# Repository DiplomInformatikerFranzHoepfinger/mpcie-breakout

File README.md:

# mpcie-breakout
https://osmocom.org/projects/mpcie-breakout/wiki --> advance this.

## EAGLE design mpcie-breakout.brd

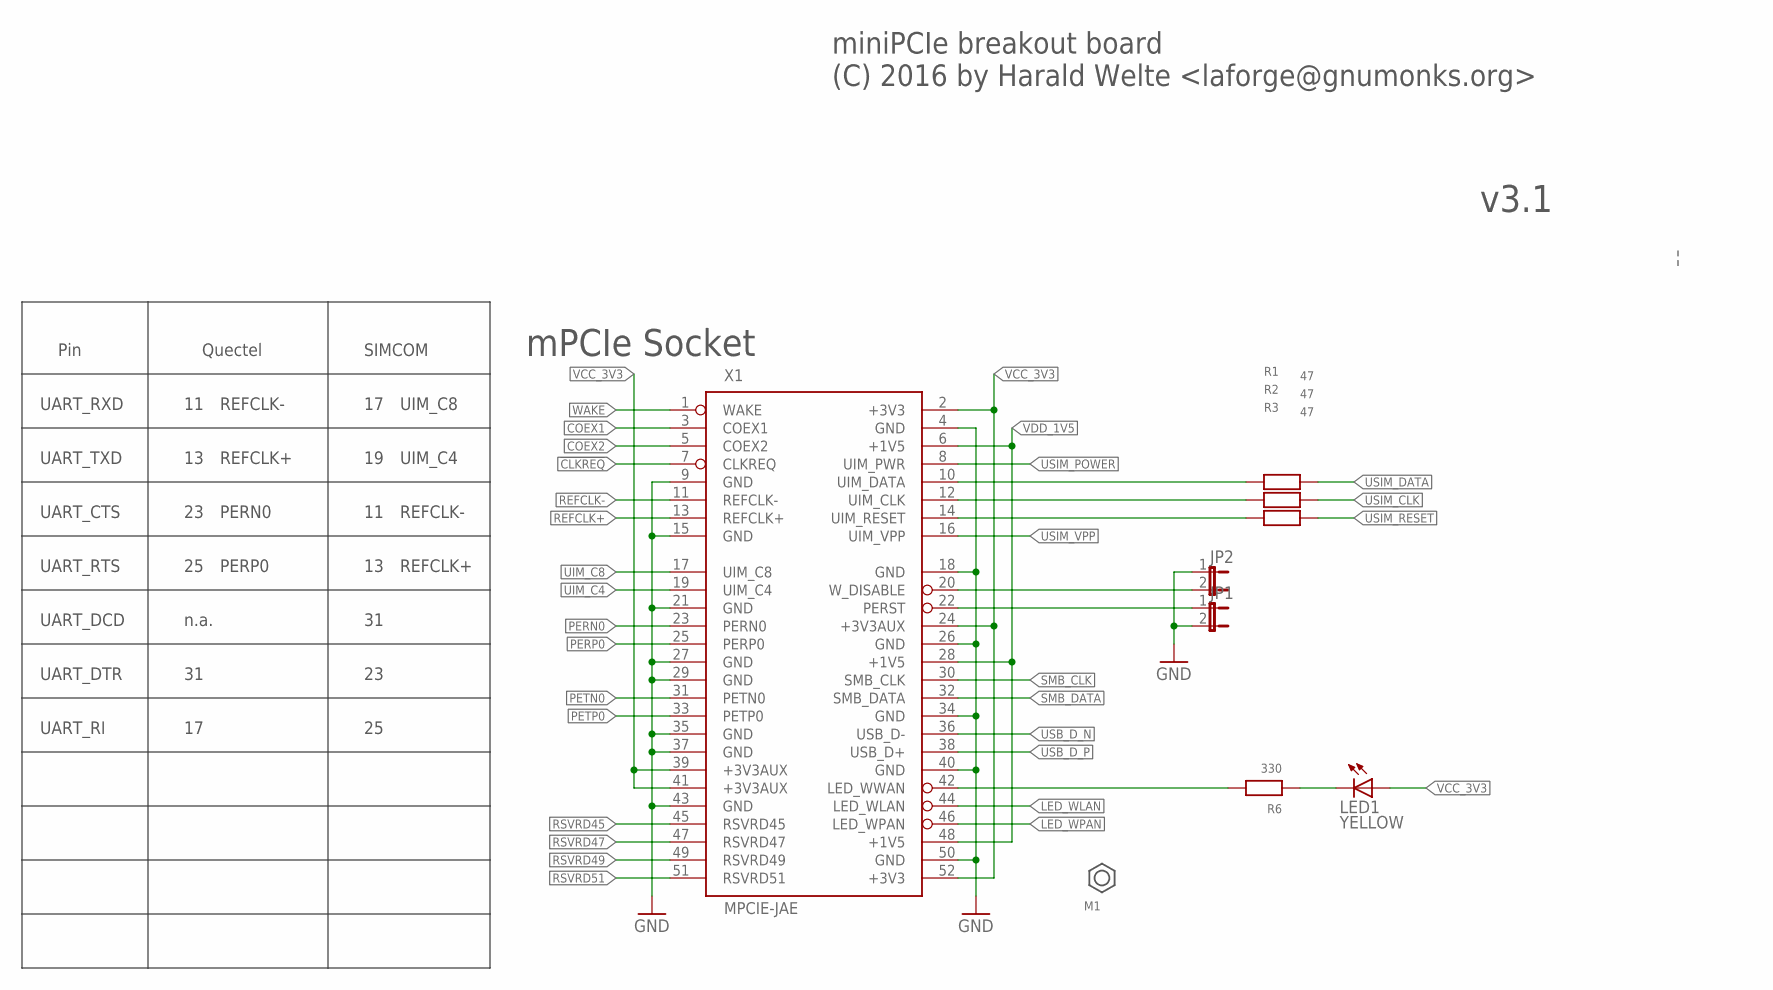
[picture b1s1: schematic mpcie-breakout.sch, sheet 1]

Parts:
JP1, JP2: JP1E; JP1; MANUFACTURERPARTNUMBER UNKNOWN MANUFACTURER PART NUMBER
LED1: YELLOW; CHIP-LED0603; MANUFACTURERPARTNUMBER UNKNOWN MANUFACTURER PART NUMBER
R1, R2, R3: 47; _0603; MANUFACTURERPARTNUMBER RC0603JR-0747RL
R6: 330; _0603; MANUFACTURERPARTNUMBER RC0603JR-07330RL
X1: MPCIE-JAE; MM60-52; MANUFACTURERPARTNUMBER MM60-52B1-E1-R650

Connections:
!CLKREQ: X1.7 (CLKREQ); also elsewhere on the board
COEX1: X1.3 (COEX1); also elsewhere on the board
COEX2: X1.5 (COEX2); also elsewhere on the board
GND: JP1.2, JP2.1, X1.4 (GND), X1.9 (GND), X1.15 (GND), X1.18 (GND), X1.21 (GND), X1.26 (GND), X1.27 (GND), X1.29 (GND), X1.34 (GND), X1.35 (GND), X1.37 (GND), X1.40 (GND), X1.43 (GND), X1.50 (GND); also elsewhere on the board
LED_WLAN: X1.44 (LED_WLAN); also elsewhere on the board
LED_WPAN: X1.46 (LED_WPAN); also elsewhere on the board
unnamed: LED1.C, R6.1
unnamed: R6.2, X1.42 (LED_WWAN)
unnamed: R1.1, X1.10 (UIM_DATA)
unnamed: R2.1, X1.12 (UIM_CLK)
unnamed: R3.1, X1.14 (UIM_RESET)
PERN0: X1.23 (PERN0); also elsewhere on the board
PERP0: X1.25 (PERP0); also elsewhere on the board
PERST: JP1.1, X1.22 (PERST)
PETN0: X1.31 (PETN0); also elsewhere on the board
PETP0: X1.33 (PETP0); also elsewhere on the board
REFCLK+: X1.13 (REFCLK+); also elsewhere on the board
REFCLK-: X1.11 (REFCLK-); also elsewhere on the board
RSVRD45: X1.45 (RSVRD45); also elsewhere on the board
RSVRD47: X1.47 (RSVRD47); also elsewhere on the board
RSVRD49: X1.49 (RSVRD49); also elsewhere on the board
RSVRD51: X1.51 (RSVRD51); also elsewhere on the board
SMB_CLK: X1.30 (SMB_CLK); also elsewhere on the board
SMB_DATA: X1.32 (SMB_DATA); also elsewhere on the board
UIM_C4: X1.19 (UIM_C4); also elsewhere on the board
UIM_C8: X1.17 (UIM_C8); also elsewhere on the board
USB_D_N: X1.36 (USB_D-); also elsewhere on the board
USB_D_P: X1.38 (USB_D+); also elsewhere on the board
USIM_CLK: R2.2; also elsewhere on the board
USIM_DATA: R1.2; also elsewhere on the board
USIM_POWER: X1.8 (UIM_PWR); also elsewhere on the board
USIM_RESET: R3.2; also elsewhere on the board
USIM_VPP: X1.16 (UIM_VPP); also elsewhere on the board
VCC_3V3: LED1.A, X1.2 (+3V3), X1.24 (+3V3AUX), X1.39 (+3V3AUX), X1.41 (+3V3AUX), X1.52 (+3V3); also elsewhere on the board
VDD_1V5: X1.6 (+1V5), X1.28 (+1V5), X1.48 (+1V5)
WAKE: X1.1 (WAKE); also elsewhere on the board
W_DISABLE: JP2.2, X1.20 (W_DISABLE)

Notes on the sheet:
miniPCIe breakout board (C) 2016 by Harald Welte <laforge@gnumonks.org>
mPCIe Socket
Quectel
SIMCOM
Pin
UART_RXD
UART_TXD
UART_CTS
UART_RTS
UART_DCD
UART_DTR
UART_RI
n.a.
REFCLK-
REFCLK+
PERN0
PERP0
UIM_C4
UIM_C8

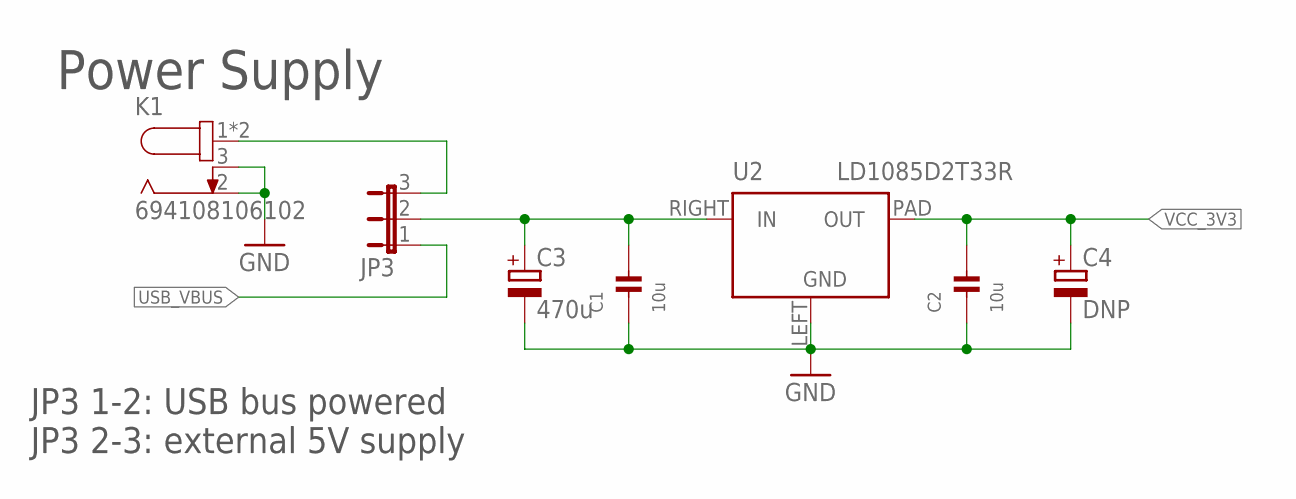
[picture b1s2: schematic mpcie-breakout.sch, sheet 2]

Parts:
C1, C2: 10u; _0805; MANUFACTURERPARTNUMBER CL21A106KOQNNNG
C3: 470u; UD-8X10_NICHICON; MANUFACTURERPARTNUMBER UUR0J471MNL1GS
C4: DNP; SMC_E; MANUFACTURERPARTNUMBER UNKNOWN MANUFACTURER PART NUMBER
JP3: JP2E; JP2; MANUFACTURERPARTNUMBER UNKNOWN MANUFACTURER PART NUMBER
K1: 694108106102; MANUFACTURERPARTNUMBER 694108106102
U2: LD1085D2T33R; ST_D2PAK; MANUFACTURERPARTNUMBER LD1085D2T33R

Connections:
GND: C1.1, C2.1, C3.-, C4.-, K1.2, K1.3, U2.LEFT (GND); also elsewhere on the board
LDO_IN: C1.2, C3.+, JP3.2, U2.RIGHT (IN)
unnamed: JP3.3, K1.1, K1.1-1 (1)
USB_VBUS: JP3.1; also elsewhere on the board
VCC_3V3: C2.2, C4.+, U2.PAD (OUT); also elsewhere on the board

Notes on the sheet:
Power Supply
JP3 1-2: USB bus powered JP3 2-3: external 5V supply

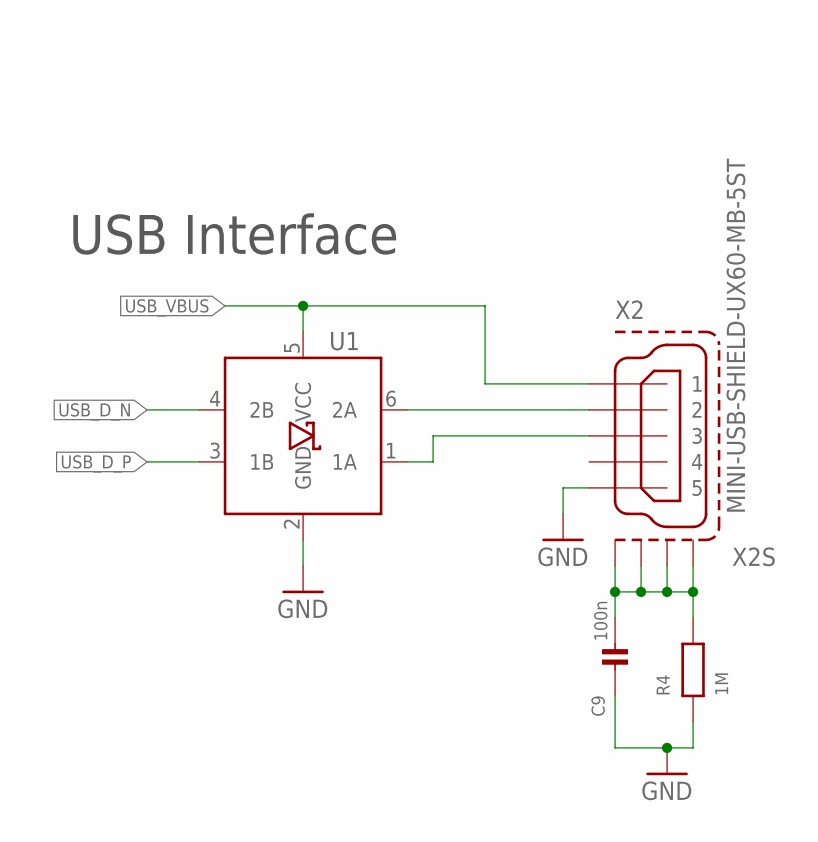
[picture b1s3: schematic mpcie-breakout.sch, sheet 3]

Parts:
C9: 100n; _0603; MANUFACTURERPARTNUMBER CL10B104KO8NNNC
R4: 1M; _0603; MANUFACTURERPARTNUMBER RC0603JR-071ML
U1: IP4234CZ6; TSOP-6; MANUFACTURERPARTNUMBER IP4234CZ6,125
X2: MINI-USB-SHIELD-UX60-MB-5ST; UX60-MB-5ST; MANUFACTURERPARTNUMBER UX60-MB-5ST

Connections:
GND: C9.1, R4.1, U1.2 (GND), X2.5; also elsewhere on the board
unnamed: C9.2, R4.2, X2.M1 (S1), X2.M2 (S2), X2.M3 (S3), X2.M4 (S4)
USB_D_N: U1.4 (2B); also elsewhere on the board
USB_D_P: U1.3 (1B); also elsewhere on the board
USB_VBUS: U1.5 (VCC), X2.1; also elsewhere on the board
_USB_D_N: U1.6 (2A), X2.2
_USB_D_P: U1.1 (1A), X2.3

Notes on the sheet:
USB Interface

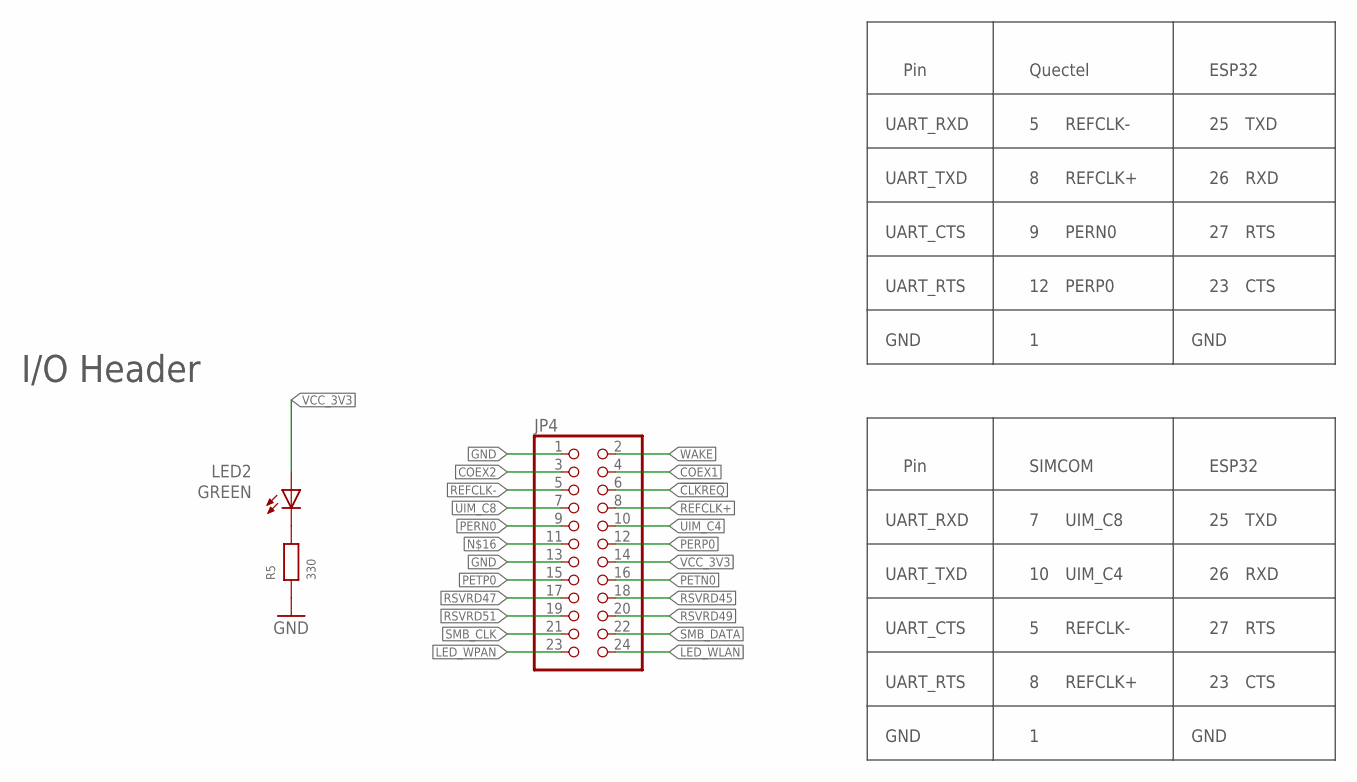
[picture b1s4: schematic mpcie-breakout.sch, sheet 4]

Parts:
JP4: PINHD-2X12; 2X12; MANUFACTURERPARTNUMBER 961224-6404-AR
LED2: GREEN; CHIP-LED0603; MANUFACTURERPARTNUMBER UNKNOWN MANUFACTURER PART NUMBER
R5: 330; _0603; MANUFACTURERPARTNUMBER RC0603JR-07330RL

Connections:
!CLKREQ: JP4.6; also elsewhere on the board
COEX1: JP4.4; also elsewhere on the board
COEX2: JP4.3; also elsewhere on the board
GND: JP4.1, JP4.13, R5.1; also elsewhere on the board
LED_WLAN: JP4.24; also elsewhere on the board
LED_WPAN: JP4.23; also elsewhere on the board
unnamed: LED2.C, R5.2
PERN0: JP4.9; also elsewhere on the board
PERP0: JP4.12; also elsewhere on the board
PETN0: JP4.16; also elsewhere on the board
PETP0: JP4.15; also elsewhere on the board
REFCLK+: JP4.8; also elsewhere on the board
REFCLK-: JP4.5; also elsewhere on the board
RSVRD45: JP4.18; also elsewhere on the board
RSVRD47: JP4.17; also elsewhere on the board
RSVRD49: JP4.20; also elsewhere on the board
RSVRD51: JP4.19; also elsewhere on the board
SMB_CLK: JP4.21; also elsewhere on the board
SMB_DATA: JP4.22; also elsewhere on the board
UIM_C4: JP4.10; also elsewhere on the board
UIM_C8: JP4.7; also elsewhere on the board
VCC_3V3: JP4.14, LED2.A; also elsewhere on the board
WAKE: JP4.2; also elsewhere on the board

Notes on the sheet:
I/O Header
Quectel
ESP32
Pin
UART_RXD
UART_TXD
UART_CTS
UART_RTS
REFCLK-
REFCLK+
PERN0
PERP0
GND
TXD
RXD
RTS
CTS
SIMCOM
UIM_C4
UIM_C8

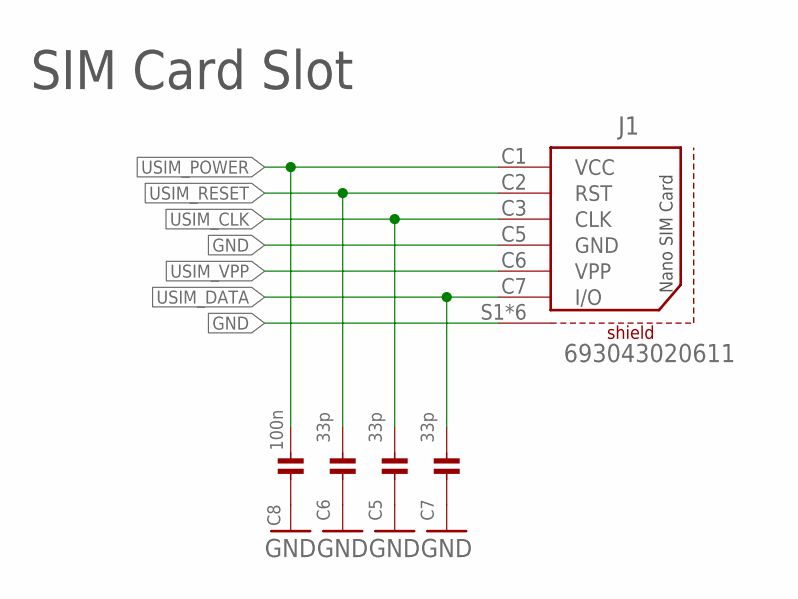
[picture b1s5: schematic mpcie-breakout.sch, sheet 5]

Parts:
C5, C6, C7: 33p; _0402; MANUFACTURERPARTNUMBER CL05C330JB5NNNC
C8: 100n; _0603; MANUFACTURERPARTNUMBER CL10B104KO8NNNC
J1: 693043020611

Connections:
GND: C5.2, C6.2, C7.2, C8.1, J1.C5 (GND), J1.S1 (SHIELD), J1.S2 (SHIELD), J1.S3 (SHIELD), J1.S4 (SHIELD), J1.S5 (SHIELD), J1.S6 (SHIELD); also elsewhere on the board
USIM_CLK: C5.1, J1.C3 (CLK); also elsewhere on the board
USIM_DATA: C7.1, J1.C7 (I/O); also elsewhere on the board
USIM_POWER: C8.2, J1.C1 (VCC); also elsewhere on the board
USIM_RESET: C6.1, J1.C2 (RST); also elsewhere on the board
USIM_VPP: J1.C6 (VPP); also elsewhere on the board

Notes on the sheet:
SIM Card Slot

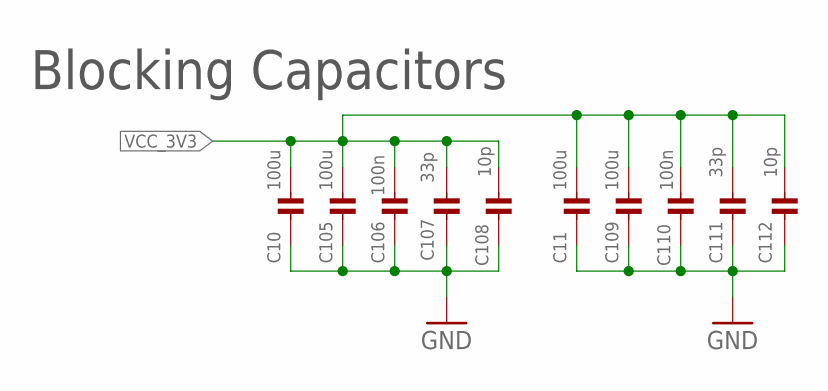
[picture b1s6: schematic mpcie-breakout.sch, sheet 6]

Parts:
C10, C11, C105, C109: 100u; 1206; MANUFACTURERPARTNUMBER GRM31CR60J107ME39K
C106, C110: 100n; _0603; MANUFACTURERPARTNUMBER CL10B104KO8NNNC
C107, C111: 33p; _0402; MANUFACTURERPARTNUMBER CL05C330JB5NNNC
C108, C112: 10p; _0603; MANUFACTURERPARTNUMBER C0603C100J5GACTU

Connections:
GND: C10.1, C11.1, C105.1, C106.1, C107.2, C108.2, C109.1, C110.1, C111.2, C112.2; also elsewhere on the board
VCC_3V3: C10.2, C11.2, C105.2, C106.2, C107.1, C108.1, C109.2, C110.2, C111.1, C112.1; also elsewhere on the board

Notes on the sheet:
Blocking Capacitors

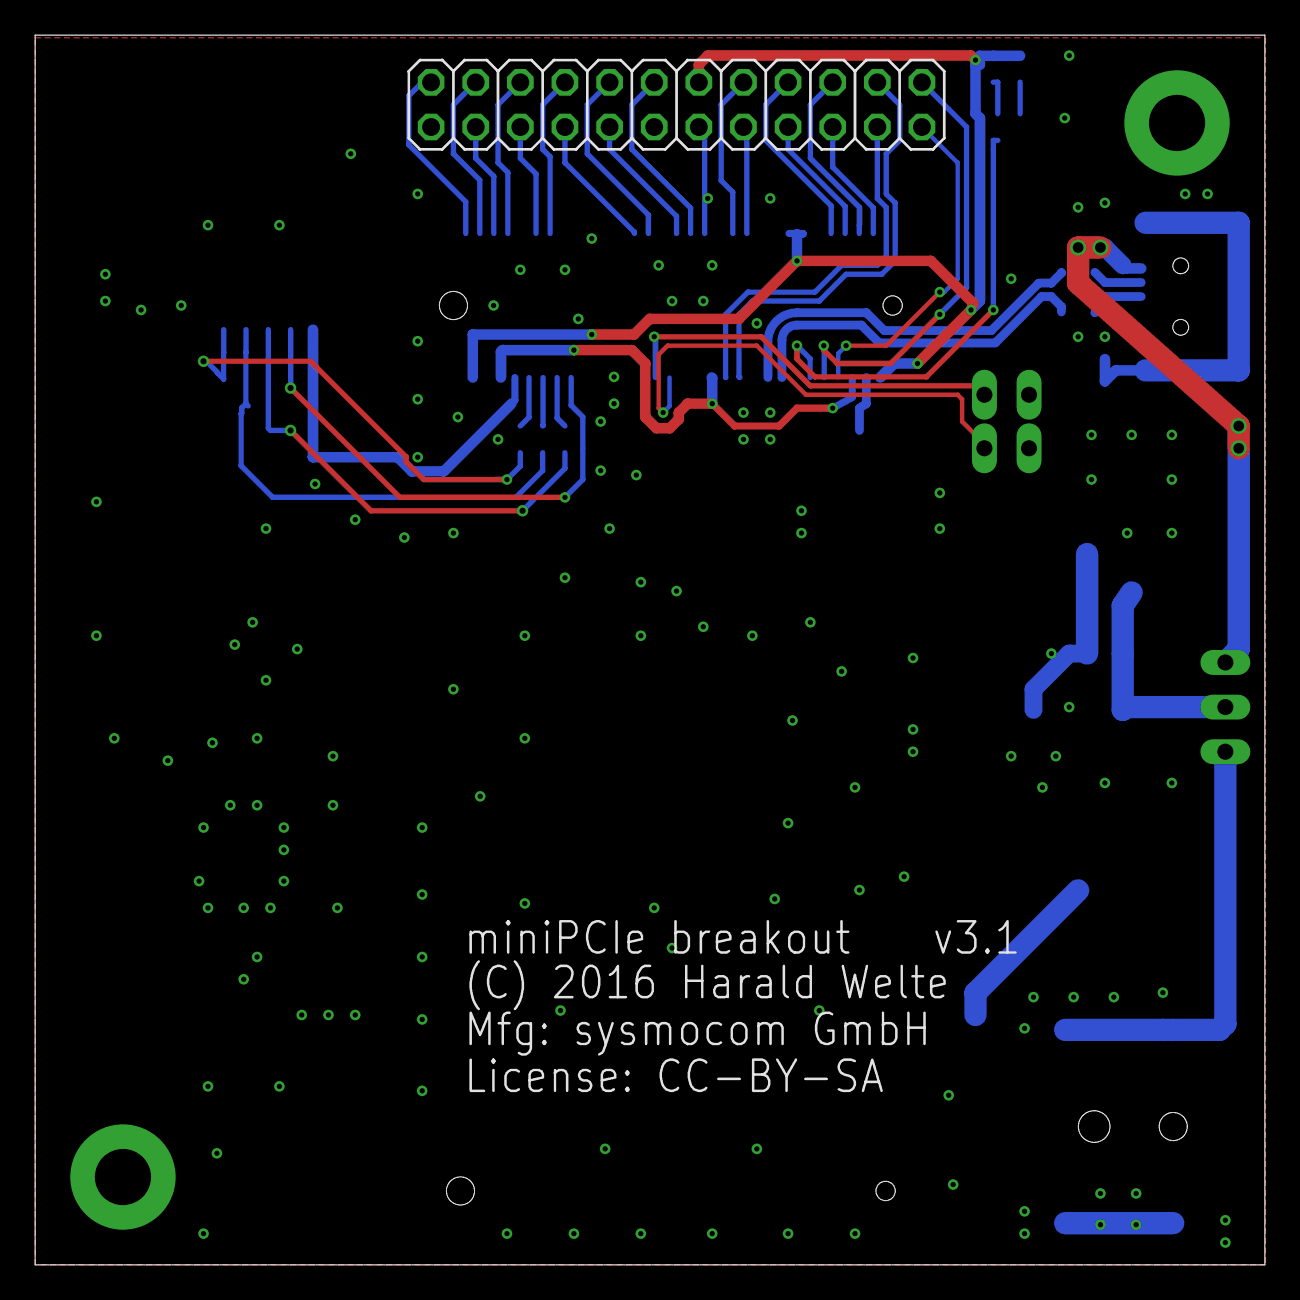
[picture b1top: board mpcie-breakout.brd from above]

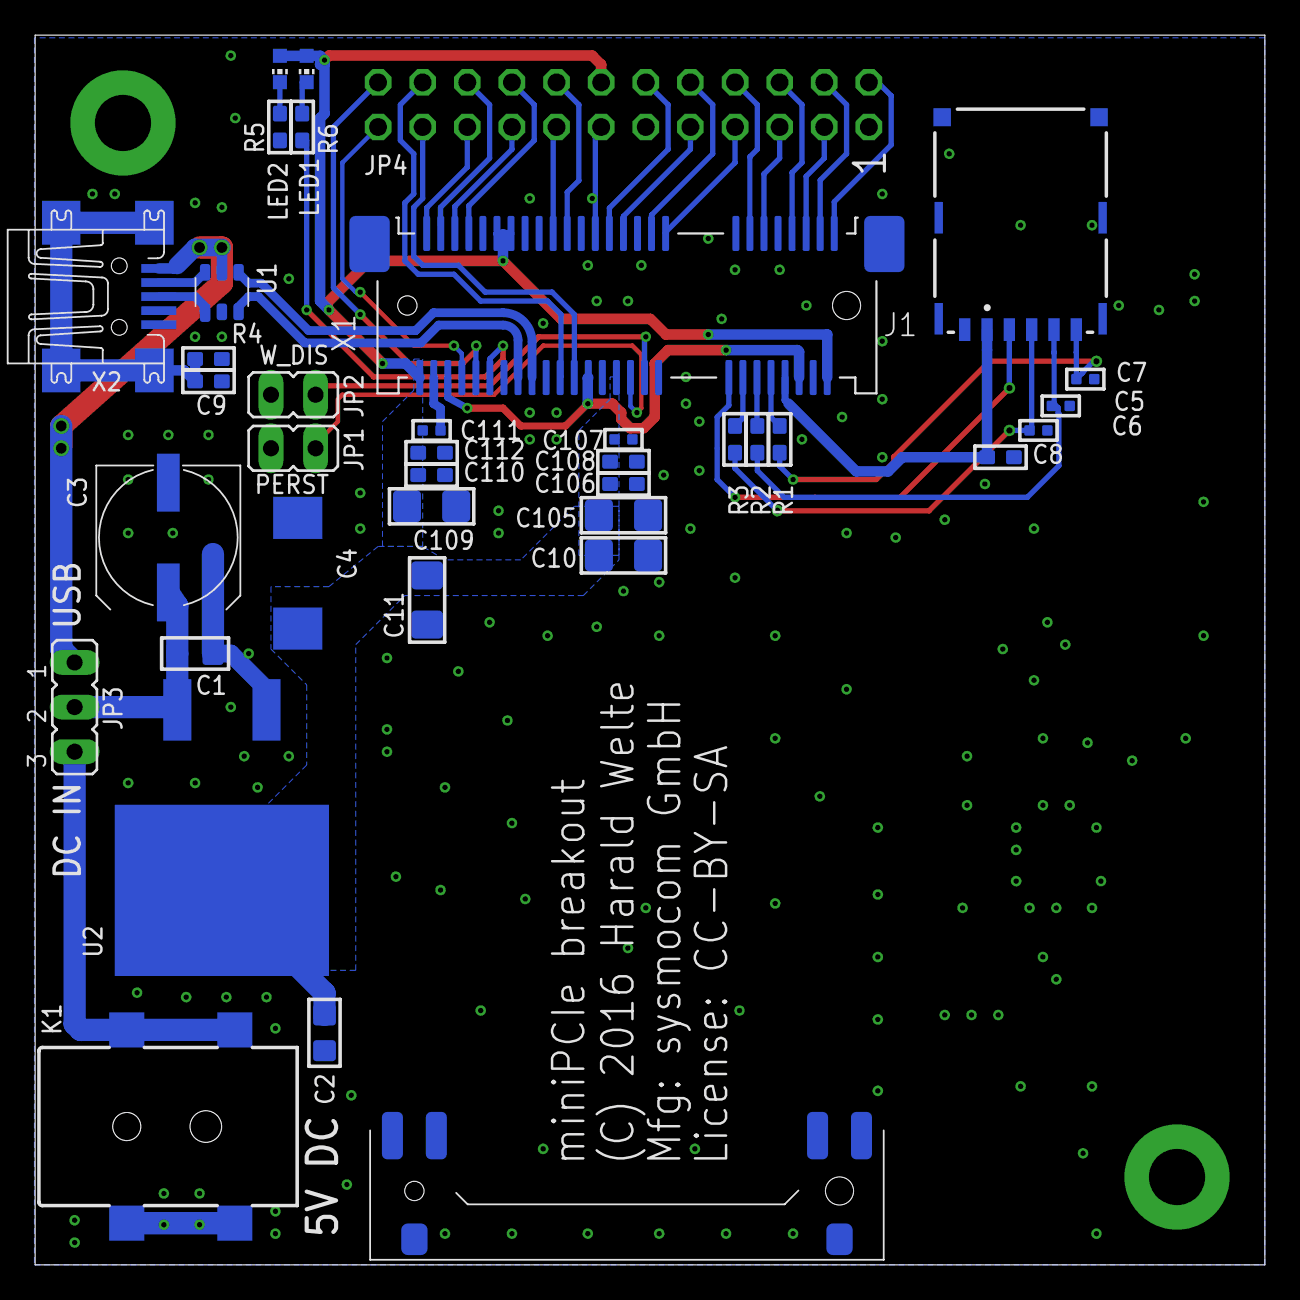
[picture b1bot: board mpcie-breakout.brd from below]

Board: 2 copper layers, 70.0 x 70.0 mm, 37 parts (36 on the bottom side), 44 nets.

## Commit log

2021-05-27 osmo-small-hardware\mpcie-breakout
    Original here: https://osmocom.org/projects/mpcie-breakout/wiki
2021-05-27 eagle Version updated.
2021-05-27 added RXD, TXD, RTS, CTS
2021-05-27 pinout defs
2021-05-27 not so easy about UART !
2021-05-27 adding XREF !
2021-05-31 libs
2021-05-31 Comments about UART.
2021-06-01 gitflow-feature-stash: nanoSIM
2021-06-01 Nano Sim placed.

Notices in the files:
mpcie-breakout.brd:
(C) 2016 Harald Welte
License: CC-BY-SA
parts and their libraries:
Wurth_Elektronik_Electromechanic_DC_Powe: Copyright: Würth Elektronik
